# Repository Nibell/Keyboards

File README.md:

# Keyboards

Welcome to the **My Custom Keyboards** repository! 🎹

## Table of Contents

- [Features](#features)
- [Repository Structure](#repository-structure)
- [License](#license)

## About

This repository includes:

- Custom keyboard designs and PCBs.

## Features

- **Custom Designs**: Schematics and files for unique keyboard builds.

## Repository Structure

- `extra/`: Schematics and files for keyboard components.
- `micropad4x4/`:  [Custom Micropad 4x4](https://github.com/Nibell/Keyboards/tree/main/micropad4x4)

## License

This project is licensed under the [MIT License](LICENSE). Feel free to use, modify, and distribute the contents of this repository in accordance with the license terms.

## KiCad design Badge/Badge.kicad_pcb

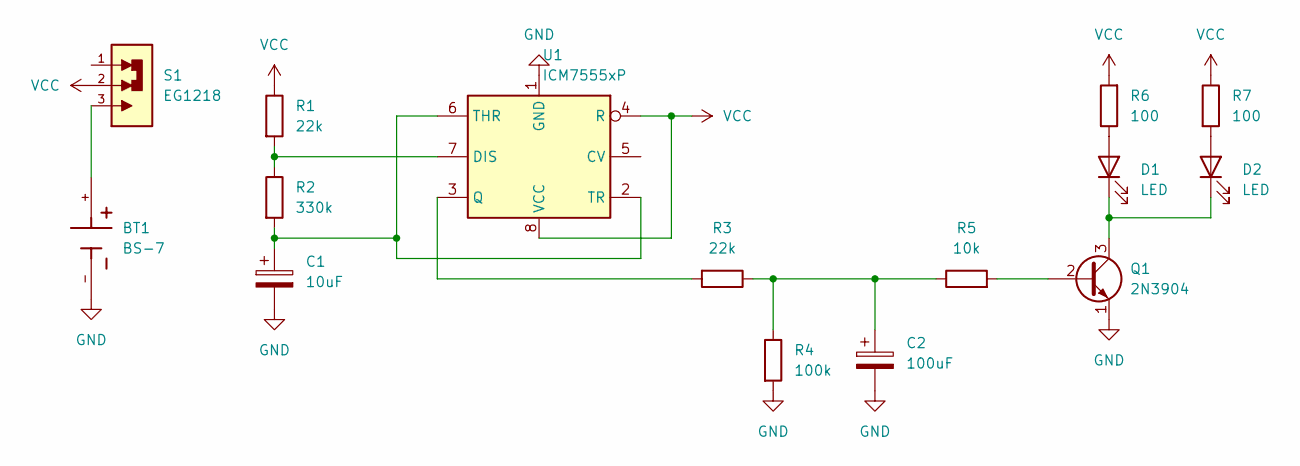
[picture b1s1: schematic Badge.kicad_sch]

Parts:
BT1: BS-7; BAT_BS-7; PARTREV H
C1: 10uF; CP_Radial_D5.0mm_P2.00mm
C2: 100uF; CP_Radial_D6.3mm_P2.50mm
D1, D2: LED; LED_D3.0mm
Q1: 2N3904; TO-92_Inline
R1, R3: 22k; R_Axial_DIN0207_L6.3mm_D2.5mm_P7.62mm_Horizontal
R2: 330k; R_Axial_DIN0207_L6.3mm_D2.5mm_P7.62mm_Horizontal
R4: 100k; R_Axial_DIN0207_L6.3mm_D2.5mm_P7.62mm_Horizontal
R5: 10k; R_Axial_DIN0207_L6.3mm_D2.5mm_P7.62mm_Horizontal
R6, R7: 100; R_Axial_DIN0207_L6.3mm_D2.5mm_P7.62mm_Horizontal
S1: EG1218; SW_EG1218
U1: ICM7555xP; DIP-8_W7.62mm

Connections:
GND: BT1.-, C1.2, C2.2, Q1.1 (E), R4.2, U1.1 (GND)
unnamed: BT1.+, S1.3
unnamed: C2.1, R3.1, R4.1, R5.1
unnamed: D1.2 (A), R6.1
unnamed: D1.1 (K), D2.1 (K), Q1.3 (C)
unnamed: D2.2 (A), R7.2
unnamed: Q1.2 (B), R5.2
unnamed: R1.2, R2.1, U1.7 (DIS)
unnamed: R3.2, U1.3 (Q)
unnamed: C1.1, R2.2, U1.2 (TR), U1.6 (THR)
VCC: R1.1, R6.2, R7.1, S1.2, U1.4 (R), U1.8 (VCC)

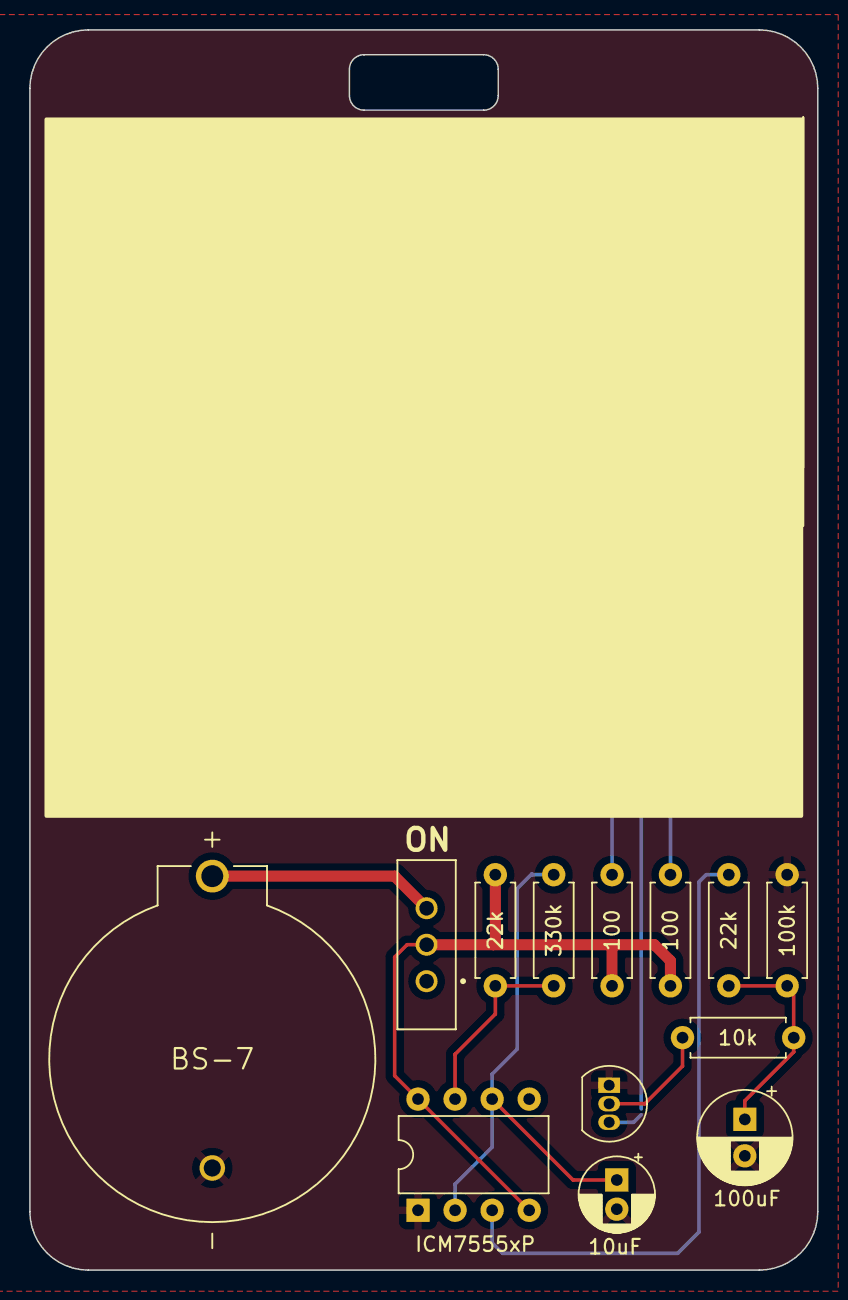
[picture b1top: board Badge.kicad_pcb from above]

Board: 2 copper layers, 54.0 x 85.0 mm, 15 parts (0 on the bottom side), 11 nets.

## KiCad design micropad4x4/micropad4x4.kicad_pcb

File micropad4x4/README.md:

# Micropad 4x4 Keyboard

## Features

- **Compact Design**: A 4x4 grid for 16 keys, perfect for shortcuts, macros, or gaming inputs.
- **Customizable Firmware**: Fully programmable using popular firmware like [QMK](https://qmk.fm/) or [VIA](https://usevia.app/).
- **Ease of Assembly**: Designed with hobbyists in mind; the build process is straightforward.
- **Versatile Use Cases**: Ideal for productivity software, video editing, music production, or gaming.
- **Open Source Hardware**: Modify the design to suit your specific needs.

## Repository Structure

- **`~`**: Contains the PCB design files for the Micropad 4x4.
- **`Production`**: Gerber and production files.
- **`Images`**: Renderings and photos of the completed macropad.

## Getting Started

### 1. Clone the Repository

To get started, clone the repository to your local machine:

```bash
git clone https://github.com/Nibell/Keyboards.git
cd Keyboards/micropad4x4
```

### 2. Gather Components

You’ll need:

- **PCB**: Fabricate the PCB using the provided Gerber files.
- **Microcontroller**: Raspberry Pi Pico.
- **Switches**: 16 mechanical switches of your choice.
- **Keycaps**: A 4x4 set.

### 3. Flash Firmware

- Install [QMK Firmware](https://docs.qmk.fm/#/newbs).
- Build and flash the firmware for your microcontroller:

  ```bash
  qmk compile -kb nibell/micropad4x4 -km default
  qmk flash -kb nibell/micropad4x4 -km default
  ```

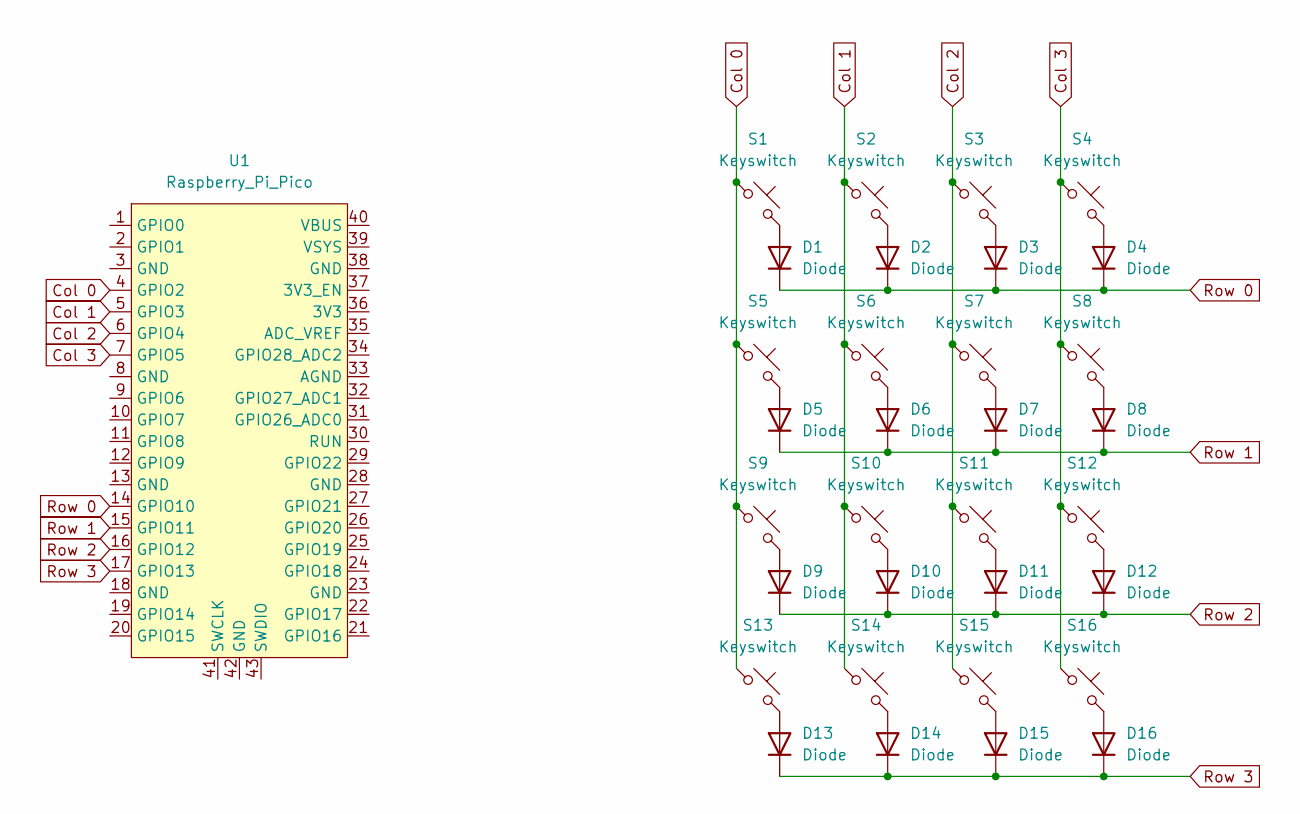
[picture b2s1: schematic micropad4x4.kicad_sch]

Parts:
D1, D2, D3, D4, D5, D6, D7, D8, D9, D10, D11, D12, D13, D14, D15, D16: Diode; Diode_DO-35
S1, S2, S3, S4, S5, S6, S7, S8, S9, S10, S11, S12, S13, S14, S15, S16: Keyswitch; MX_PCB_1.00u
U1: Raspberry_Pi_Pico

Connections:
Col 0: S1.1, S5.1, S9.1, S13.1, U1.4 (GPIO2)
Col 1: S2.1, S6.1, S10.1, S14.1, U1.5 (GPIO3)
Col 2: S3.1, S7.1, S11.1, S15.1, U1.6 (GPIO4)
Col 3: S4.1, S8.1, S12.1, S16.1, U1.7 (GPIO5)
unnamed: D1.2 (A), S1.2
unnamed: D2.2 (A), S2.2
unnamed: D3.2 (A), S3.2
unnamed: D4.2 (A), S4.2
unnamed: D5.2 (A), S5.2
unnamed: D6.2 (A), S6.2
unnamed: D7.2 (A), S7.2
unnamed: D8.2 (A), S8.2
unnamed: D9.2 (A), S9.2
unnamed: D10.2 (A), S10.2
unnamed: D11.2 (A), S11.2
unnamed: D12.2 (A), S12.2
unnamed: D13.2 (A), S13.2
unnamed: D14.2 (A), S14.2
unnamed: D15.2 (A), S15.2
unnamed: D16.2 (A), S16.2
Row 0: D1.1 (K), D2.1 (K), D3.1 (K), D4.1 (K), U1.14 (GPIO10)
Row 1: D5.1 (K), D6.1 (K), D7.1 (K), D8.1 (K), U1.15 (GPIO11)
Row 2: D9.1 (K), D10.1 (K), D11.1 (K), D12.1 (K), U1.16 (GPIO12)
Row 3: D13.1 (K), D14.1 (K), D15.1 (K), D16.1 (K), U1.17 (GPIO13)

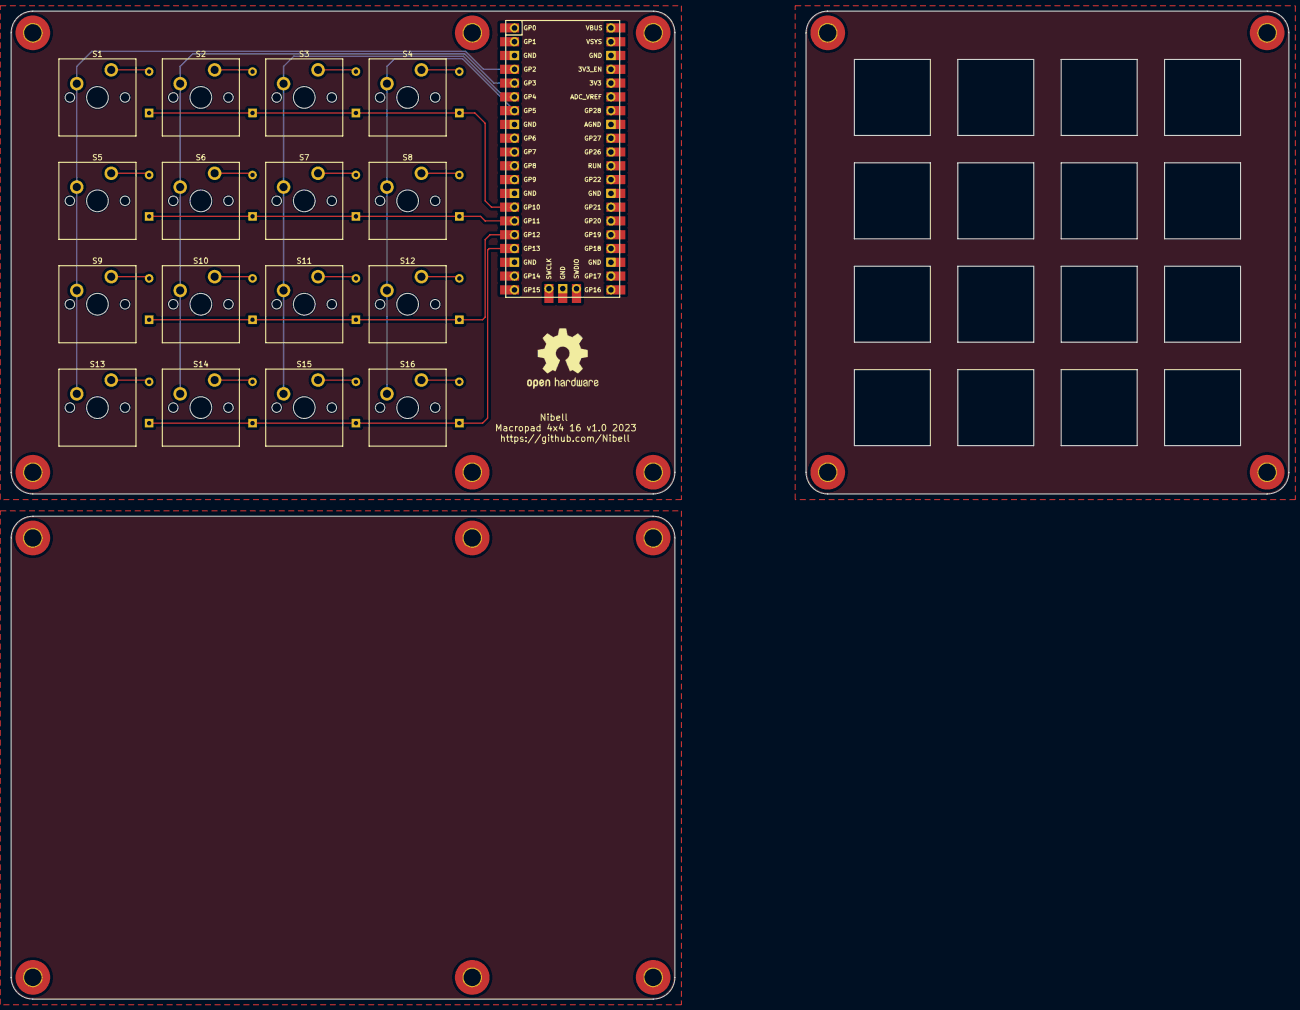
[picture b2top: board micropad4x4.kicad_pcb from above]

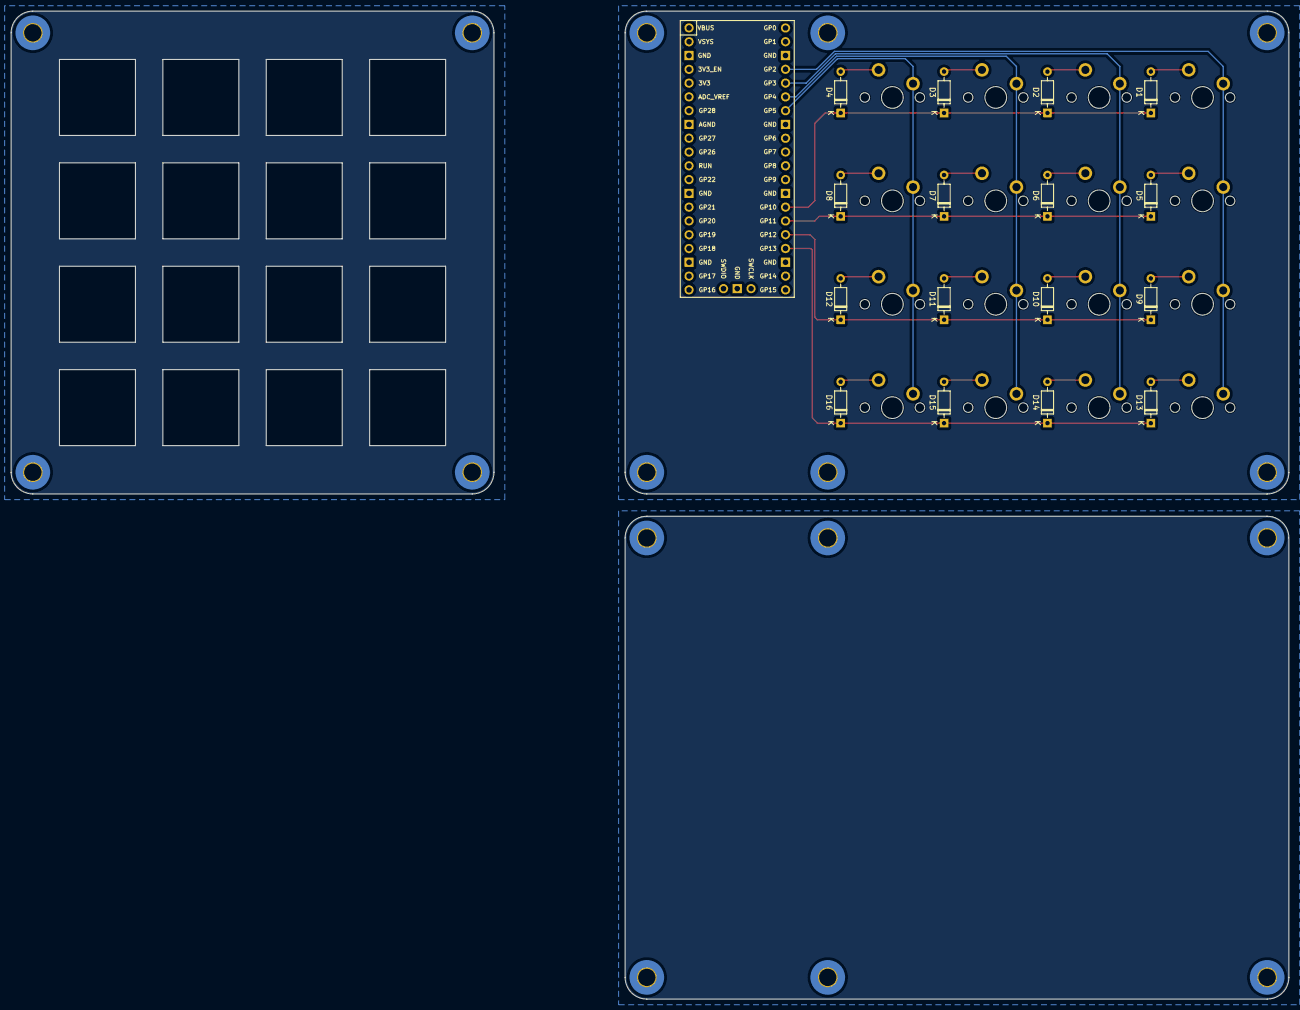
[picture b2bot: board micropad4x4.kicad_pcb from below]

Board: 2 copper layers, 235.4 x 182.0 mm, 33 parts (16 on the bottom side), 24 nets.

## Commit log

2023-11-24 Added KiCad modules
2023-11-24 renamed to extra
2023-11-24 added micro pad
2023-11-24 renamed to old
2023-11-24 fixed 3d models
2023-11-24 removed old schema
2023-11-24 updated pcb
2023-11-26 update pcb
2023-12-21 added top layer
2023-12-21 minor changes
2023-12-21 fixed errors
2023-12-21 added gerber files
2023-12-22 fixed dimensions
2023-12-22 version 1 done
2023-12-22 backup
2023-12-23 added separate gerber files
2023-12-23 added zip for pcb
2023-12-24 Added logo and smaller base
2023-12-25 final version
2023-12-25 removed not needed trace
2023-12-29 renamed to micropad4x4
2023-12-29 removed old files
2023-12-29 removed not needed file
2024-01-09 backups
2024-01-10 badge done
2024-01-12 added backups
2024-11-30 feat: removed old keyboard
2024-11-30 feat: added readme
2024-11-30 feat: added readme for micorpad
2024-11-30 chore: updated readme
